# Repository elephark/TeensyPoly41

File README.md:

# TeensyPoly41

This is loosely based on [TeensyPoly6](https://github.com/albnys/TeensyPoly6)'s schematic, but with many changes of various significance:

* It uses a Teensy 4.1, as the 3.5 wasn't available when this was designed (and is now discontinued).
* It takes the form of a single 2-layer PCB with all pots, switches, and buttons directly affixed. I suppose you could run wires to a front panel if you *really* wanted to.
* It leans much more heavily into the multiplexers, with 8 instead of 1. This results in a more efficient use of pins. 
* It adds a few more controls and enables full ADSR envelopes on the amp and filter.
* It adds LEDs to indicate system state (and greatly aid debugging).
* It adds a rotary dial to select the desired MIDI channel.

### What it looks like

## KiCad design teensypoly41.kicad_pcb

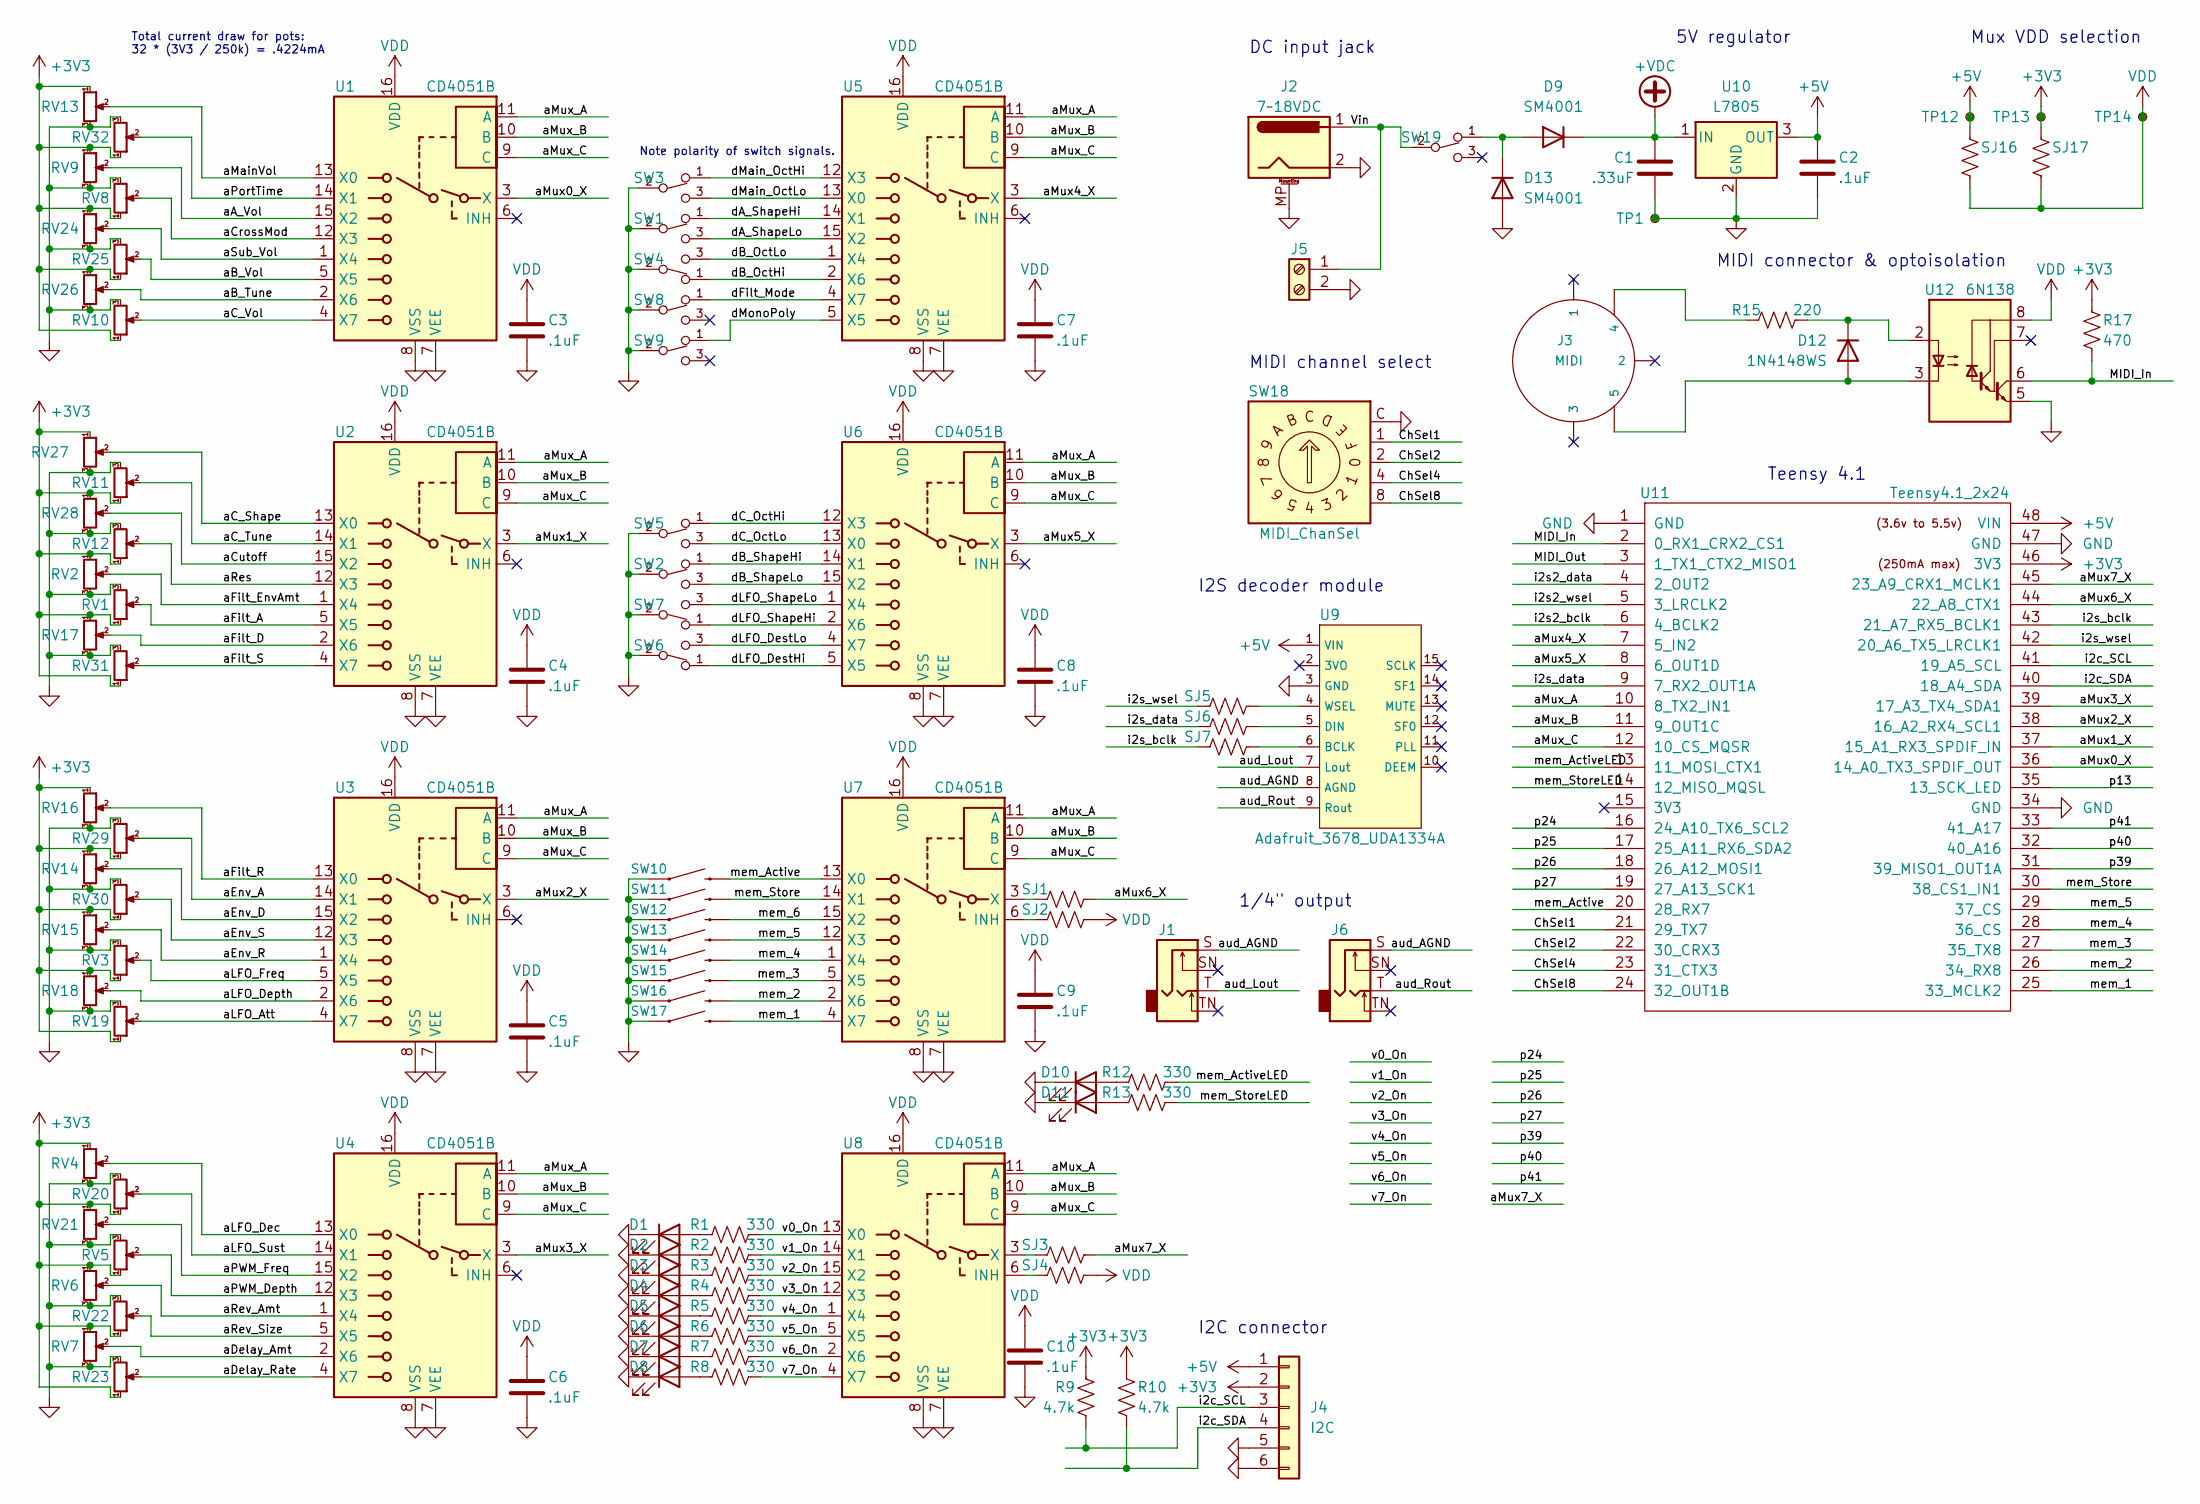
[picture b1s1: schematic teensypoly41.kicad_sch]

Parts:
C1: .33uF; C_0805_2012Metric_Pad1.18x1.45mm_HandSolder
C2, C3, C4, C5, C6, C7, C8, C9, C10: .1uF; C_0805_2012Metric_Pad1.18x1.45mm_HandSolder
D1: voice0; LED_0805_2012Metric_Pad1.15x1.40mm_HandSolder
D2: voice1; LED_0805_2012Metric_Pad1.15x1.40mm_HandSolder
D3: voice2; LED_0805_2012Metric_Pad1.15x1.40mm_HandSolder
D4: voice3; LED_0805_2012Metric_Pad1.15x1.40mm_HandSolder
D5: voice4; LED_0805_2012Metric_Pad1.15x1.40mm_HandSolder
D6: voice5; LED_0805_2012Metric_Pad1.15x1.40mm_HandSolder
D7: voice6; LED_0805_2012Metric_Pad1.15x1.40mm_HandSolder
D8: voice7; LED_0805_2012Metric_Pad1.15x1.40mm_HandSolder
D9, D13: SM4001; D_MELF
D10: MemActive; LED_0805_2012Metric_Pad1.15x1.40mm_HandSolder
D11: MemStore; LED_0805_2012Metric_Pad1.15x1.40mm_HandSolder
D12: 1N4148WS; D_SOD-323
J1: AudioJack_L; Jack_6.35mm_Neutrik_NMJ4HFD2_Horizontal
J2: 7~18VDC; BarrelJack_CUI_PJ-063AH_Horizontal
J3: MIDI; DIN5-RA-PTH
J4: I2C; MOLEX-1X6_LOCK
J5: Screw_Terminal_01x02; TerminalBlock_Phoenix_MKDS-1,5-2-5.08_1x02_P5.08mm_Horizont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
J6: AudioJack_R; Jack_6.35mm_Neutrik_NMJ4HFD2_Horizontal
R1, R2, R3, R4, R5, R6, R7, R8, R12, R13: 330; R_0603_1608Metric
R9, R10: 4.7k; R_0603_1608Metric
R15: 220; R_0603_1608Metric
R17: 470; R_0603_1608Metric
RV1: Filt_A; Alps_RS301111J00J
RV2: Filt_EnvAmt; Alps_RS301111J00J
RV3: LFO_Freq; Alps_RS301111J00J
RV4: LFO_D; Alps_RS301111J00J
RV5: PWM_Depth; Alps_RS301111J00J
RV6: Rev_Amt; Alps_RS301111J00J
RV7: Delay_Amt; Alps_RS301111J00J
RV8: CrossMod; Alps_RS301111J00J
RV9: OscA_Vol; Alps_RS301111J00J
RV10: OscC_Vol; Alps_RS301111J00J
RV11: OscC_Tune; Alps_RS301111J00J
RV12: Filt_Res; Alps_RS301111J00J
RV13: MainVolume; Alps_RS301111J00J
RV14: Env_D; Alps_RS301111J00J
RV15: Env_R; Alps_RS301111J00J
RV16: Filt_R; Alps_RS301111J00J
RV17: Filt_D; Alps_RS301111J00J
RV18: LFO_Depth; Alps_RS301111J00J
RV19: LFO_A; Alps_RS301111J00J
RV20: LFO_S; Alps_RS301111J00J
RV21: PWM_Freq; Alps_RS301111J00J
RV22: Rev_Size; Alps_RS301111J00J
RV23: Delay_Rate; Alps_RS301111J00J
RV24: Sub_Vol; Alps_RS301111J00J
RV25: OscB_Vol; Alps_RS301111J00J
RV26: OscB_Tune; Alps_RS301111J00J
RV27: OscC_Shape; Alps_RS301111J00J
RV28: Filt_Cutoff; Alps_RS301111J00J
RV29: Env_A; Alps_RS301111J00J
RV30: Env_S; Alps_RS301111J00J
RV31: Filt_S; Alps_RS301111J00J
RV32: PortTime; Alps_RS301111J00J
SJ1, SJ2, SJ3, SJ4, SJ5, SJ6, SJ7, SJ16, SJ17: 0; R_0603_1608Metric
SW1: OscA_Shape; E-Switch_SPDT
SW2: OscB_Shape; E-Switch_SPDT
SW3: Main_Oct; E-Switch_SPDT
SW4: OscB_Oct; E-Switch_SPDT
SW5: OscC_Oct; E-Switch_SPDT
SW6: LFO_Dest; E-Switch_SPDT
SW7: LFO_Shape; E-Switch_SPDT
SW8: Filt_Mode; E-Switch_SPDT
SW9: Mono/Poly; E-Switch_SPDT
SW10: Mem_Active; TACTILE_SWITCH_PTH_12MM
SW11: Mem_Store; TACTILE_SWITCH_PTH_12MM
SW12: Mem_6; TACTILE_SWITCH_PTH_12MM
SW13: Mem_5; TACTILE_SWITCH_PTH_12MM
SW14: Mem_4; TACTILE_SWITCH_PTH_12MM
SW15: Mem_3; TACTILE_SWITCH_PTH_12MM
SW16: Mem_2; TACTILE_SWITCH_PTH_12MM
SW17: Mem_1; TACTILE_SWITCH_PTH_12MM
SW18: MIDI_ChanSel; Nidec_Copal_SH-7010B
SW19: SW_SPDT_ON-ON; E-Switch_SPDT
TP1: GND; TestPoint_Loop_D1.80mm_Drill1.0mm_Beaded
TP12: 5V; TestPoint_Loop_D1.80mm_Drill1.0mm_Beaded
TP13: 3V3; TestPoint_Loop_D1.80mm_Drill1.0mm_Beaded
TP14: VDD; TestPoint_Loop_D1.80mm_Drill1.0mm_Beaded
U1, U2, U3, U4, U5, U6, U7, U8: CD4051B; SOIC-16_3.9x9.9mm_P1.27mm
U9: Adafruit_3678_UDA1334A
U10: L7805; TO-252-2
U11: Teensy4.1_2x24
U12: 6N138; DIP-8_W8.89mm_SMDSocket_LongPads

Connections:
+3V3: J4.2, R9.1, R10.1, R17.1, RV1.1, RV2.1, RV3.1, RV4.1, RV5.1, RV6.1, RV7.1, RV8.1, RV9.1, RV10.1, RV11.1, RV12.1, RV13.1, RV14.1, RV15.1, RV16.1, RV17.1, RV18.1, RV19.1, RV20.1, RV21.1, RV22.1, RV23.1, RV24.1, RV25.1, RV26.1, RV27.1, RV28.1, RV29.1, RV30.1, RV31.1, RV32.1, SJ17.1, TP13.1, U11.46 (3V3)
+5V: C2.1, J4.1, SJ16.1, TP12.1, U9.1 (VIN), U10.3 (OUT), U11.48 (VIN)
+VDC: C1.1, D9.1 (K), U10.1 (IN)
/ChSel1: SW18.1, U11.21 (29_TX7)
/ChSel2: SW18.2, U11.22 (30_CRX3)
/ChSel4: SW18.4, U11.23 (31_CTX3)
/ChSel8: SW18.8, U11.24 (32_OUT1B)
/MIDI_In: R17.2, U11.2 (0_RX1_CRX2_CS1), U12.6 (VO2)
/MIDI_Out: U11.3 (1_TX1_CTX2_MISO1)
/Vin: J2.1, J5.1, SW19.2 (B)
/aA_Vol: RV9.2, U1.15 (X2)
/aB_Tune: RV26.2, U1.2 (X6)
/aB_Vol: RV25.2, U1.5 (X5)
/aC_Shape: RV27.2, U2.13 (X0)
/aC_Tune: RV11.2, U2.14 (X1)
/aC_Vol: RV10.2, U1.4 (X7)
/aCrossMod: RV8.2, U1.12 (X3)
/aCutoff: RV28.2, U2.15 (X2)
/aDelay_Amt: RV7.2, U4.2 (X6)
/aDelay_Rate: RV23.2, U4.4 (X7)
/aEnv_A: RV29.2, U3.14 (X1)
/aEnv_D: RV14.2, U3.15 (X2)
/aEnv_R: RV15.2, U3.1 (X4)
/aEnv_S: RV30.2, U3.12 (X3)
/aFilt_A: RV1.2, U2.5 (X5)
/aFilt_D: RV17.2, U2.2 (X6)
/aFilt_EnvAmt: RV2.2, U2.1 (X4)
/aFilt_R: RV16.2, U3.13 (X0)
/aFilt_S: RV31.2, U2.4 (X7)
/aLFO_Att: RV19.2, U3.4 (X7)
/aLFO_Dec: RV4.2, U4.13 (X0)
/aLFO_Depth: RV18.2, U3.2 (X6)
/aLFO_Freq: RV3.2, U3.5 (X5)
/aLFO_Sust: RV20.2, U4.14 (X1)
/aMainVol: RV13.2, U1.13 (X0)
/aMux0_X: U1.3 (X), U11.36 (14_A0_TX3_SPDIF_OUT)
/aMux1_X: U2.3 (X), U11.37 (15_A1_RX3_SPDIF_IN)
/aMux2_X: U3.3 (X), U11.38 (16_A2_RX4_SCL1)
/aMux3_X: U4.3 (X), U11.39 (17_A3_TX4_SDA1)
/aMux4_X: U5.3 (X), U11.7 (5_IN2)
/aMux5_X: U6.3 (X), U11.8 (6_OUT1D)
/aMux6_X: SJ1.2, U11.44 (22_A8_CTX1)
/aMux7_X: SJ3.2, U11.45 (23_A9_CRX1_MCLK1)
/aMux_A: U1.11 (A), U2.11 (A), U3.11 (A), U4.11 (A), U5.11 (A), U6.11 (A), U7.11 (A), U8.11 (A), U11.10 (8_TX2_IN1)
/aMux_B: U1.10 (B), U2.10 (B), U3.10 (B), U4.10 (B), U5.10 (B), U6.10 (B), U7.10 (B), U8.10 (B), U11.11 (9_OUT1C)
/aMux_C: U1.9 (C), U2.9 (C), U3.9 (C), U4.9 (C), U5.9 (C), U6.9 (C), U7.9 (C), U8.9 (C), U11.12 (10_CS_MQSR)
/aPWM_Depth: RV5.2, U4.12 (X3)
/aPWM_Freq: RV21.2, U4.15 (X2)
/aPortTime: RV32.2, U1.14 (X1)
/aRes: RV12.2, U2.12 (X3)
/aRev_Amt: RV6.2, U4.1 (X4)
/aRev_Size: RV22.2, U4.5 (X5)
/aSub_Vol: RV24.2, U1.1 (X4)
/aud_AGND: J1.S, J6.S, U9.8 (AGND)
/aud_Lout: J1.T, U9.7 (Lout)
/aud_Rout: J6.T, U9.9 (Rout)
/dA_ShapeHi: SW1.1 (A), U5.14 (X1)
/dA_ShapeLo: SW1.3 (C), U5.15 (X2)
/dB_OctHi: SW4.1 (A), U5.2 (X6)
/dB_OctLo: SW4.3 (C), U5.1 (X4)
/dB_ShapeHi: SW2.1 (A), U6.14 (X1)
/dB_ShapeLo: SW2.3 (C), U6.15 (X2)
/dC_OctHi: SW5.1 (A), U6.12 (X3)
/dC_OctLo: SW5.3 (C), U6.13 (X0)
/dFilt_Mode: SW8.1 (A), U5.4 (X7)
/dLFO_DestHi: SW6.1 (A), U6.5 (X5)
/dLFO_DestLo: SW6.3 (C), U6.4 (X7)
/dLFO_ShapeHi: SW7.1 (A), U6.2 (X6)
/dLFO_ShapeLo: SW7.3 (C), U6.1 (X4)
/dMain_OctHi: SW3.1 (A), U5.12 (X3)
/dMain_OctLo: SW3.3 (C), U5.13 (X0)
/dMonoPoly: SW9.1 (A), U5.5 (X5)
/i2c_SCL: J4.3, R9.2, U11.41 (19_A5_SCL)
/i2c_SDA: J4.4, R10.2, U11.40 (18_A4_SDA)
/i2s2_bclk: U11.6 (4_BCLK2)
/i2s2_data: U11.4 (2_OUT2)
/i2s2_wsel: U11.5 (3_LRCLK2)
/i2s_bclk: SJ7.2, U11.43 (21_A7_RX5_BCLK1)
/i2s_data: SJ6.2, U11.9 (7_RX2_OUT1A)
/i2s_wsel: SJ5.2, U11.42 (20_A6_TX5_LRCLK1)
/mem_1: SW17.3 (2), U7.4 (X7), U11.25 (33_MCLK2)
/mem_2: SW16.3 (2), U7.2 (X6), U11.26 (34_RX8)
/mem_3: SW15.3 (2), U7.5 (X5), U11.27 (35_TX8)
/mem_4: SW14.3 (2), U7.1 (X4), U11.28 (36_CS)
/mem_5: SW13.3 (2), U7.12 (X3), U11.29 (37_CS)
/mem_6: SW12.3 (2), U7.15 (X2)
/mem_Active: SW10.3 (2), U7.13 (X0), U11.20 (28_RX7)
/mem_ActiveLED: R12.2, U11.13 (11_MOSI_CTX1)
/mem_Store: SW11.3 (2), U7.14 (X1), U11.30 (38_CS1_IN1)
/mem_StoreLED: R13.2, U11.14 (12_MISO_MQSL)
/p13: U11.35 (13_SCK_LED)
/p24: U11.16 (24_A10_TX6_SCL2)
/p25: U11.17 (25_A11_RX6_SDA2)
/p26: U11.18 (26_A12_MOSI1)
/p27: U11.19 (27_A13_SCK1)
/p39: U11.31 (39_MISO1_OUT1A)
/p40: U11.32 (40_A16)
/p41: U11.33 (41_A17)
/v0_On: R1.2, U8.13 (X0)
/v1_On: R2.2, U8.14 (X1)
/v2_On: R3.2, U8.15 (X2)
/v3_On: R4.2, U8.12 (X3)
/v4_On: R5.2, U8.1 (X4)
/v5_On: R6.2, U8.5 (X5)
/v6_On: R7.2, U8.2 (X6)
/v7_On: R8.2, U8.4 (X7)
GND: C1.2, C2.2, C3.2, C4.2, C5.2, C6.2, C7.2, C8.2, C9.2, C10.2, D1.1 (K), D2.1 (K), D3.1 (K), D4.1 (K), D5.1 (K), D6.1 (K), D7.1 (K), D8.1 (K), D10.1 (K), D11.1 (K), D13.2 (A), J2.2, J2.MP (MountPin), J4.5, J4.6, J5.2, RV1.3, RV2.3, RV3.3, RV4.3, RV5.3, RV6.3, RV7.3, RV8.3, RV9.3, RV10.3, RV11.3, RV12.3, RV13.3, RV14.3, RV15.3, RV16.3, RV17.3, RV18.3, RV19.3, RV20.3, RV21.3, RV22.3, RV23.3, RV24.3, RV25.3, RV26.3, RV27.3, RV28.3, RV29.3, RV30.3, RV31.3, RV32.3, SW1.2 (B), SW2.2 (B), SW3.2 (B), SW4.2 (B), SW5.2 (B), SW6.2 (B), SW7.2 (B), SW8.2 (B), SW9.2 (B), SW10.1, SW11.1, SW12.1, SW13.1, SW14.1, SW15.1, SW16.1, SW17.1, SW18.C, TP1.1, U1.7 (VEE), U1.8 (VSS), U2.7 (VEE), U2.8 (VSS), U3.7 (VEE), U3.8 (VSS), U4.7 (VEE), U4.8 (VSS), U5.7 (VEE), U5.8 (VSS), U6.7 (VEE), U6.8 (VSS), U7.7 (VEE), U7.8 (VSS), U8.7 (VEE), U8.8 (VSS), U9.3 (GND), U10.2 (GND), U11.1 (GND), U11.34 (GND), U11.47 (GND), U12.5 (GND)
unnamed: D1.2 (A), R1.1
unnamed: D2.2 (A), R2.1
unnamed: D3.2 (A), R3.1
unnamed: D4.2 (A), R4.1
unnamed: D5.2 (A), R5.1
unnamed: D6.2 (A), R6.1
unnamed: D7.2 (A), R7.1
unnamed: D8.2 (A), R8.1
unnamed: D10.2 (A), R12.1
unnamed: D11.2 (A), R13.1
unnamed: D12.1 (K), R15.2, U12.2 (C1)
unnamed: D12.2 (A), J3.5, U12.3 (C2)
unnamed: D9.2 (A), D13.1 (K), SW19.1 (A)
unnamed: J3.4, R15.1
unnamed: SJ1.1, U7.3 (X)
unnamed: SJ2.1, U7.6 (INH)
unnamed: SJ3.1, U8.3 (X)
unnamed: SJ4.1, U8.6 (INH)
unnamed: SJ5.1, U9.4 (WSEL)
unnamed: SJ6.1, U9.5 (DIN)
unnamed: SJ7.1, U9.6 (BCLK)
VDD: C3.1, C4.1, C5.1, C6.1, C7.1, C8.1, C9.1, C10.1, SJ2.2, SJ4.2, SJ16.2, SJ17.2, TP14.1, U1.16 (VDD), U2.16 (VDD), U3.16 (VDD), U4.16 (VDD), U5.16 (VDD), U6.16 (VDD), U7.16 (VDD), U8.16 (VDD), U12.8 (VCC)

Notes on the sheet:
Mux VDD selection
Total current draw for pots: 32 * (3V3 / 250k) = .4224mA
I2S decoder module
Teensy 4.1
DC input jack
MIDI channel select
I2C connector
MIDI connector & optoisolation
Note polarity of switch signals.
1/4" output
5V regulator

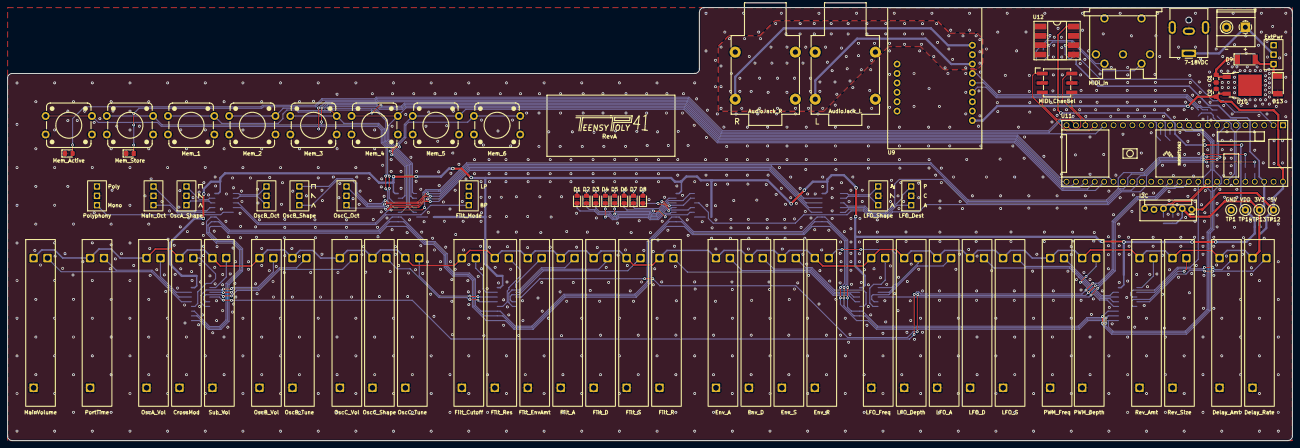
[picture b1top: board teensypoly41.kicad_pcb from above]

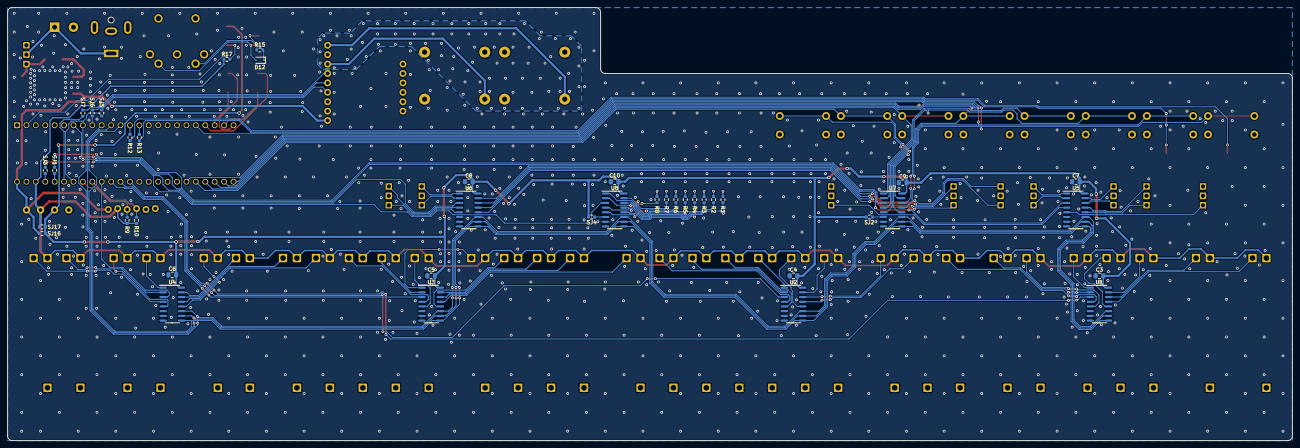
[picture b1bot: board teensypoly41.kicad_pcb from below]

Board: 2 copper layers, 346.7 x 116.8 mm, 119 parts (40 on the bottom side), 117 nets.

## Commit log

2023-08-22 Initial commit, which is also RevA.
2023-10-14 Added images of RevA finished build.
